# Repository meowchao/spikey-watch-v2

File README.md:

# spikey watch 

- KiCad 10
- 2-layer PCB stackup

---

# Current Status

- [x] Schematic Complete
- [x] PCB Routing
- [ ] PCB Manufactured
- [ ] Bring-up
- [ ] Firmware Development
- [ ] Deep Sleep Optimization

---

---

---

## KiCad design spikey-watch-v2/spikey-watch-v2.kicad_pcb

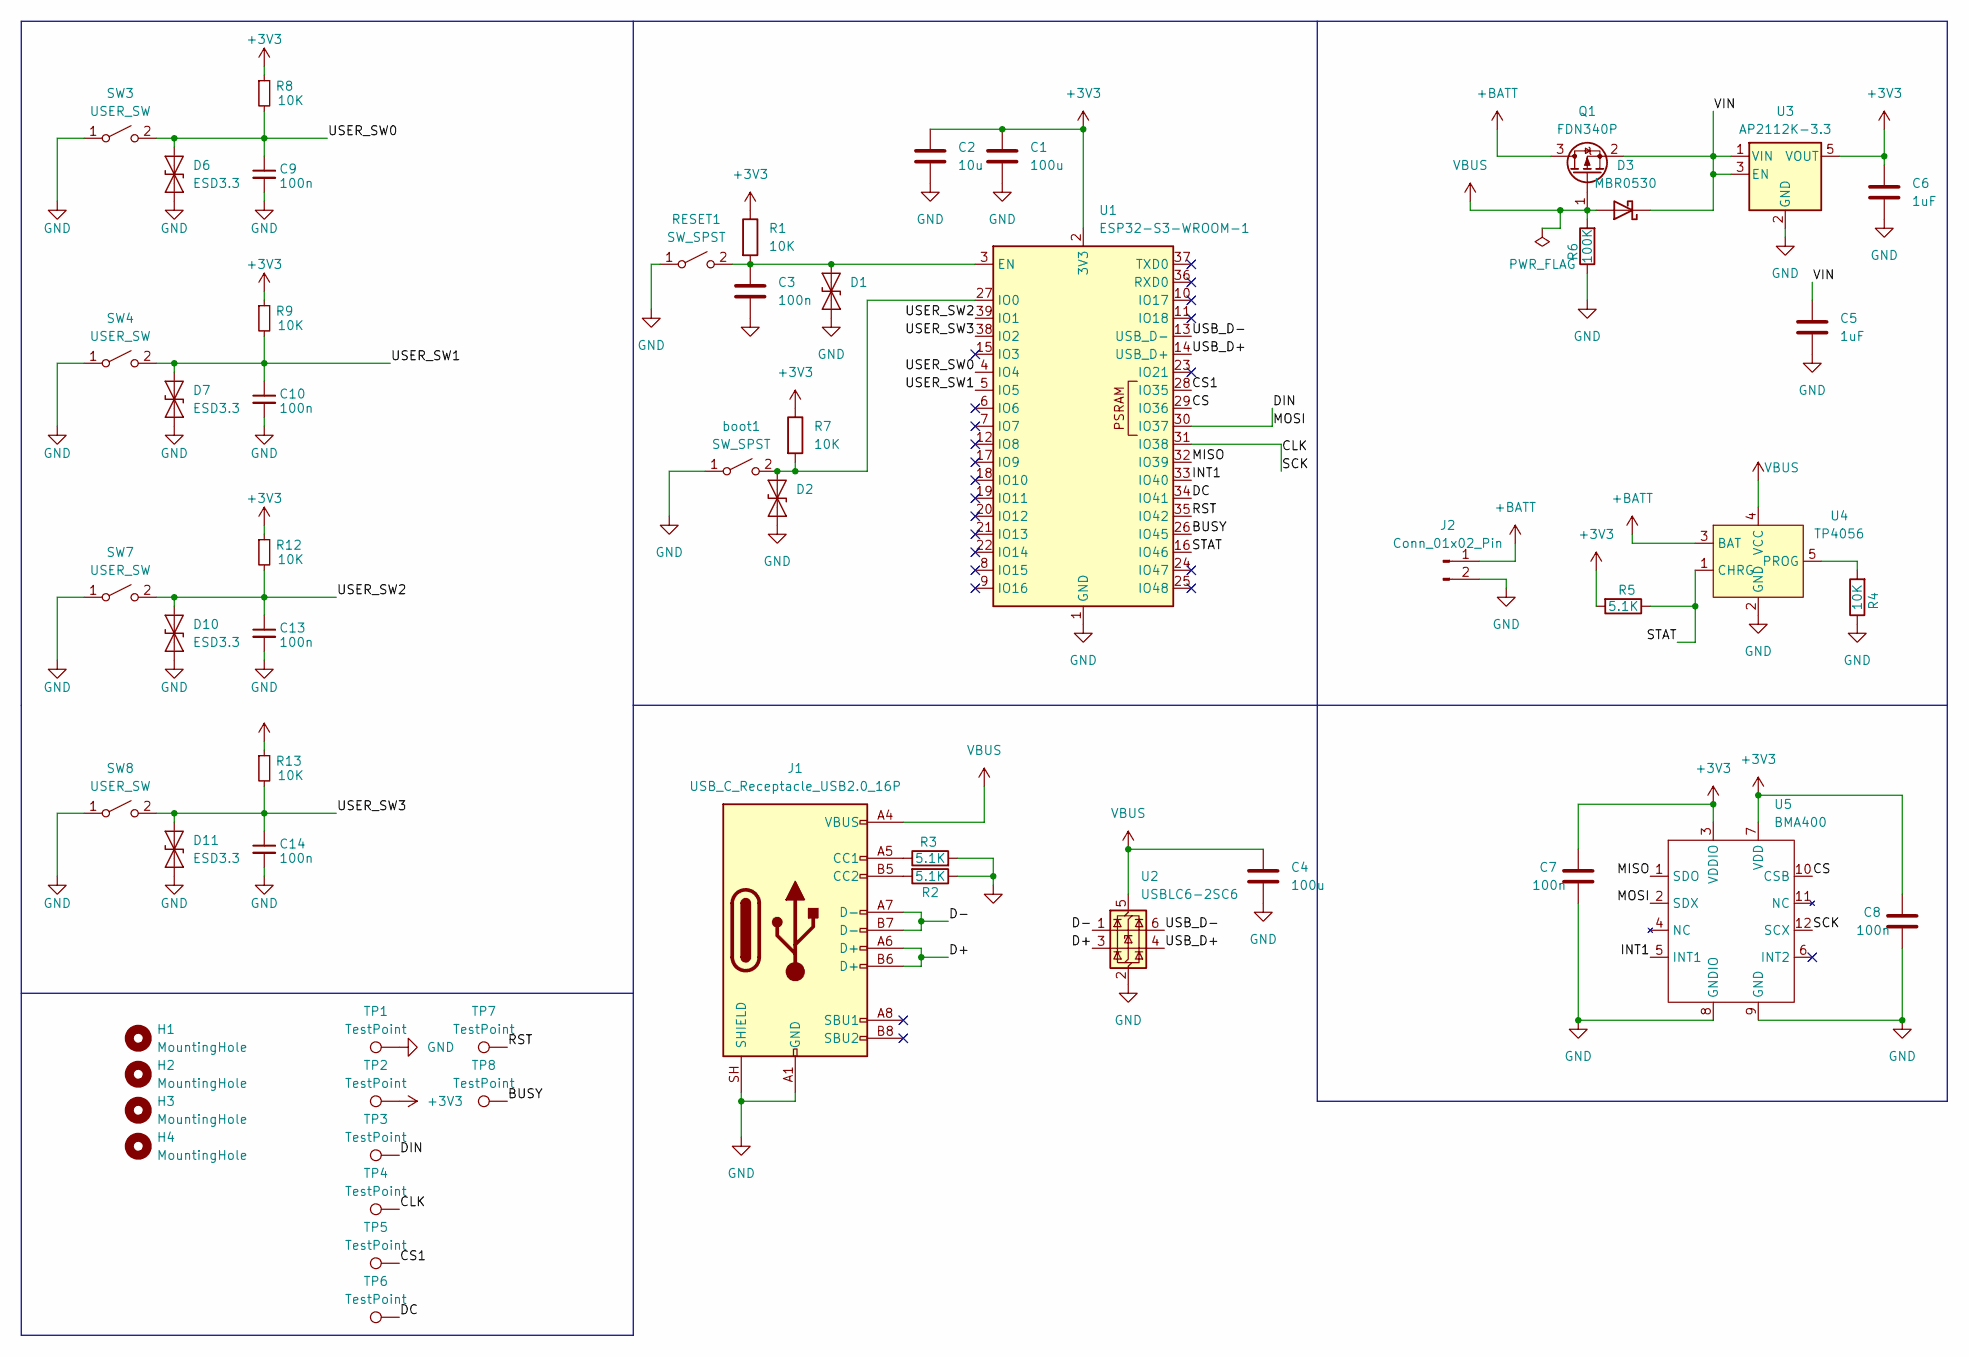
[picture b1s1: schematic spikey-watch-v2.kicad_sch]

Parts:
C1, C4: 100u; C_0603_1608Metric
C2: 10u; C_0603_1608Metric
C3, C7, C8, C9, C10, C13, C14: 100n; C_0603_1608Metric
C5, C6: 1uF; C_0603_1608Metric
D1, D2: ESD9B3.3ST5G; D_SOD-923
D3: MBR0530; D_SOD-123
D6, D7, D10, D11: ESD3.3; D_SOD-923
H1, H2, H3, H4: MountingHole; MountingHole_3.2mm_M3
J1: USB_C_Receptacle_USB2.0_16P; USB_C_Receptacle_GCT_USB4105-xx-A_16P_TopMnt_Horizontal
J2: Conn_01x02_Pin; Molex_Micro-Latch_53253-0270_1x02_P2.00mm_Vertical
Q1: FDN340P; SOT-23
R1, R4, R7, R8, R9, R12, R13: 10K; R_0603_1608Metric
R2, R3, R5: 5.1K; R_0603_1608Metric
R6: 100K; R_0603_1608Metric
RESET1: SW_SPST; SW_SPST_B3U-1000P
SW3, SW4, SW7, SW8: USER_SW; Panasonic_EVQPUL_EVQPUC
TP1, TP2, TP3, TP4, TP5, TP6, TP7, TP8: TestPoint; TestPoint_Pad_1.0x1.0mm
U1: ESP32-S3-WROOM-1
U2: USBLC6-2SC6; SOT-23-6
U3: AP2112K-3.3; SOT-23-5
U4: TP4056; SOT-23-5
U5: BMA400; LGA-12_2x2mm_P0.5mm
boot1: SW_SPST; SW_SPST_B3U-1000P

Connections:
+3V3: C1.1, C2.1, C6.1, C7.1, C8.1, R1.1, R5.2, R7.1, R8.1, R9.1, R12.1, R13.1, TP2.1 (1_1), U1.2 (3V3), U3.5 (VOUT), U5.3 (VDDIO), U5.7 (VDD)
+BATT: J2.1, Q1.3 (D), U4.3 (BAT)
/BUSY: TP8.1 (1_1), U1.26 (IO45)
/CLK: TP4.1 (1_1), U1.31 (IO38), U5.12 (SCX)
/CS: U1.29 (IO36), U5.10 (CSB)
/CS1: TP5.1 (1_1), U1.28 (IO35)
/D+: J1.A6 (D+), J1.B6 (D+), U2.3 (I/O2)
/D-: J1.A7 (D-), J1.B7 (D-), U2.1 (I/O1)
/DC: TP6.1 (1_1), U1.34 (IO41)
/DIN: TP3.1 (1_1), U1.30 (IO37), U5.2 (SDX)
/INT1: U1.33 (IO40), U5.5 (INT1)
/MISO: U1.32 (IO39), U5.1 (SDO)
/RST: TP7.1 (1_1), U1.35 (IO42)
/STAT: R5.1, U1.16 (IO46), U4.1 (CHRG)
/USB_D+: U1.14 (USB_D+), U2.4 (I/O2)
/USB_D-: U1.13 (USB_D-), U2.6 (I/O1)
/USER_SW0: C9.1, D6.2 (A2), R8.2, SW3.2 (B), U1.4 (IO4)
/USER_SW1: C10.1, D7.2 (A2), R9.2, SW4.2 (B), U1.5 (IO5)
/USER_SW2: C13.1, D10.2 (A2), R12.2, SW7.2 (B), U1.39 (IO1)
/USER_SW3: C14.1, D11.2 (A2), R13.2, SW8.2 (B), U1.38 (IO2)
/VIN: C5.1, D3.1 (K), Q1.2 (S), U3.1 (VIN), U3.3 (EN)
GND: C1.2, C2.2, C3.2, C4.2, C5.2, C6.2, C7.2, C8.2, C9.2, C10.2, C13.2, C14.2, D1.2 (A2), D2.2 (A2), D6.1 (A1), D7.1 (A1), D10.1 (A1), D11.1 (A1), J1.A1 (GND), J1.A12 (GND), J1.B1 (GND), J1.B12 (GND), J1.SH (SHIELD), J2.2, R2.1, R3.2, R4.1, R6.1, RESET1.1 (A), SW3.1 (A), SW4.1 (A), SW7.1 (A), SW8.1 (A), TP1.1 (1_1), U1.1 (GND), U1.40 (GND), U1.41 (GND), U2.2 (GND), U3.2 (GND), U4.2 (GND), U5.8 (GNDIO), U5.9 (GND), boot1.1 (A)
unnamed: C3.1, D1.1 (A1), R1.2, RESET1.2 (B), U1.3 (EN)
unnamed: D2.1 (A1), R7.2, U1.27 (IO0), boot1.2 (B)
unnamed: J1.A5 (CC1), R3.1
unnamed: J1.B5 (CC2), R2.2
unnamed: R4.2, U4.5 (PROG)
VBUS: C4.1, D3.2 (A), J1.A4 (VBUS), J1.A9 (VBUS), J1.B4 (VBUS), J1.B9 (VBUS), Q1.1 (G), R6.2, U2.5 (VBUS), U4.4 (VCC)

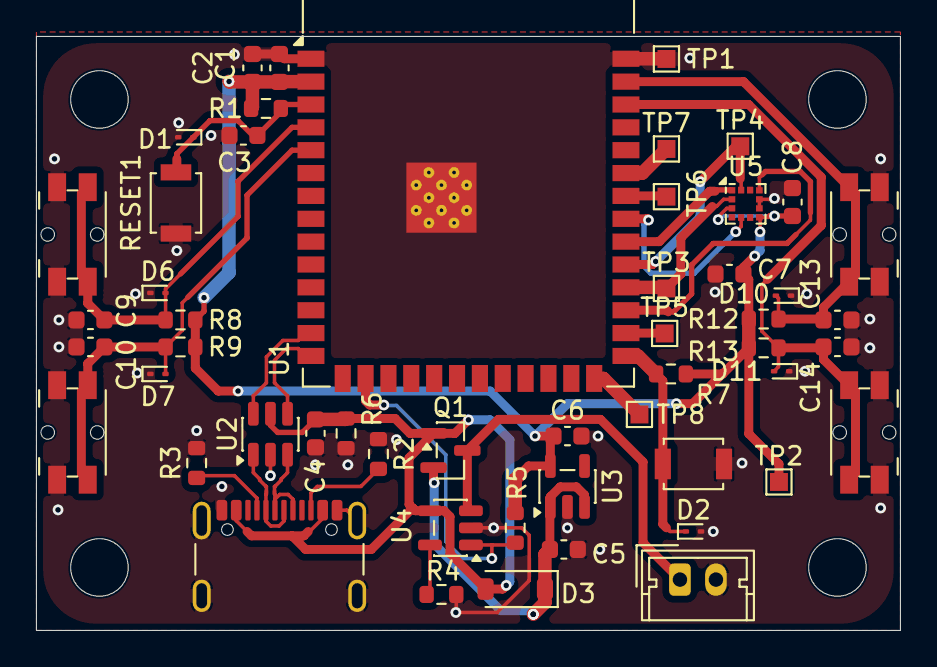
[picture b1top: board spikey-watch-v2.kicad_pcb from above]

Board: 2 copper layers, 48.0 x 33.0 mm, 56 parts (0 on the bottom side), 28 nets.

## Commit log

2026-05-24 improved routing
